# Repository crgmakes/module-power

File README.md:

# Simple Power Module

All the source files for the simple power module hardware. This module converts 120VAC or 240VAC to 5VDC @ 2A and also provides 3.3V @ 3A.

# Software 

You will need [KiCad](https://kicad.org) to view and edit this design. Click [here](https://www.kicad.org/download/) to download.

You will also need all the associated libraries and models to drive the design if you want to make changes or view the 3D rendering:

https://github.com/crgmakes/kicad-library.git

Kicad MUST be configured properly to use all the files in this repo. Once you have Kicad installed, under Preferences->Configure Paths..., make the following entries:

1 - KICAD_USER_DIR -> set to the root location of where you placed the above repository.
2 - KICAD_USER_LIBRARY = ${KICAD_USER_DIR}/Library
3 - KICAD_USER_MODEL_DIR = ${KICAD_USER_LIBRARY}/models
4 - KICAD_USER_TEMPLATE_DIR	= ${KICAD_USER_LIBRARY}/templates	

Kicad will operate mostly normally if these are not set properly. You will notice an issue when you view the PCB in 3D mode.

***NOTE***: after makeing a release build in git, if your rendered 3D images are missing components, ensure the path to EVERY component model is set to ${KICAD_USER_MODEL_DIR}/<model name>.

Kicad sometimes replaces the variable with an expansion and that FAILS during the build process because the expanded variable is local and does not match the build environment.

---

THE DESIGN IS PROVIDED "AS IS" AND THE AUTHOR DISCLAIMS ALL WARRANTIES WITH REGARD TO THIS DESIGN INCLUDING ALL IMPLIED WARRANTIES OF MERCHANTABILITY AND FITNESS. IN NO EVENT SHALL THE AUTHOR BE LIABLE FOR ANY SPECIAL, DIRECT, INDIRECT, OR CONSEQUENTIAL DAMAGES OR ANY DAMAGES WHATSOEVER RESULTING FROM LOSS OF USE, DATA OR PROFITS, WHETHER IN AN ACTION OF CONTRACT, NEGLIGENCE OR OTHER TORTIOUS ACTION, ARISING OUT OF OR IN CONNECTION WITH THE USE OR PERFORMANCE OF THIS DESIGN.

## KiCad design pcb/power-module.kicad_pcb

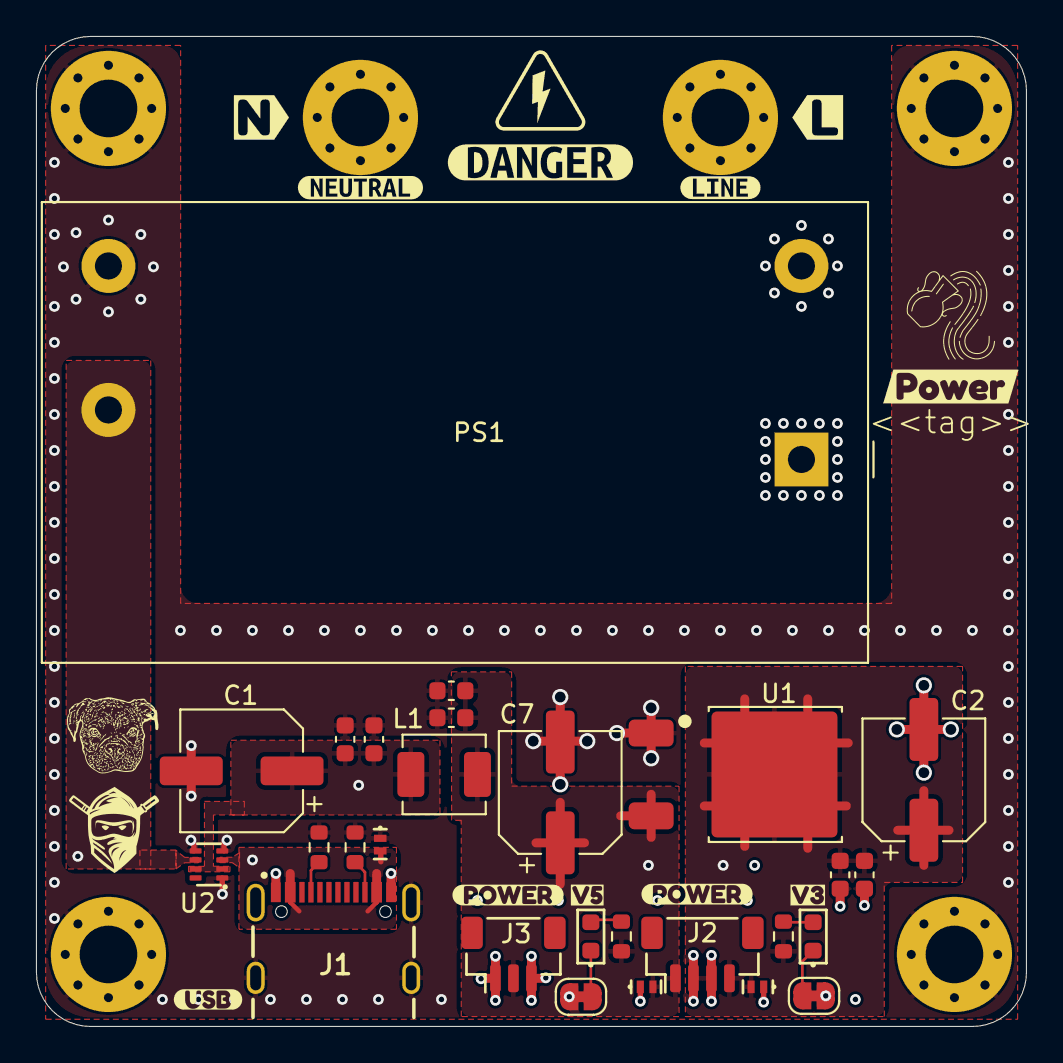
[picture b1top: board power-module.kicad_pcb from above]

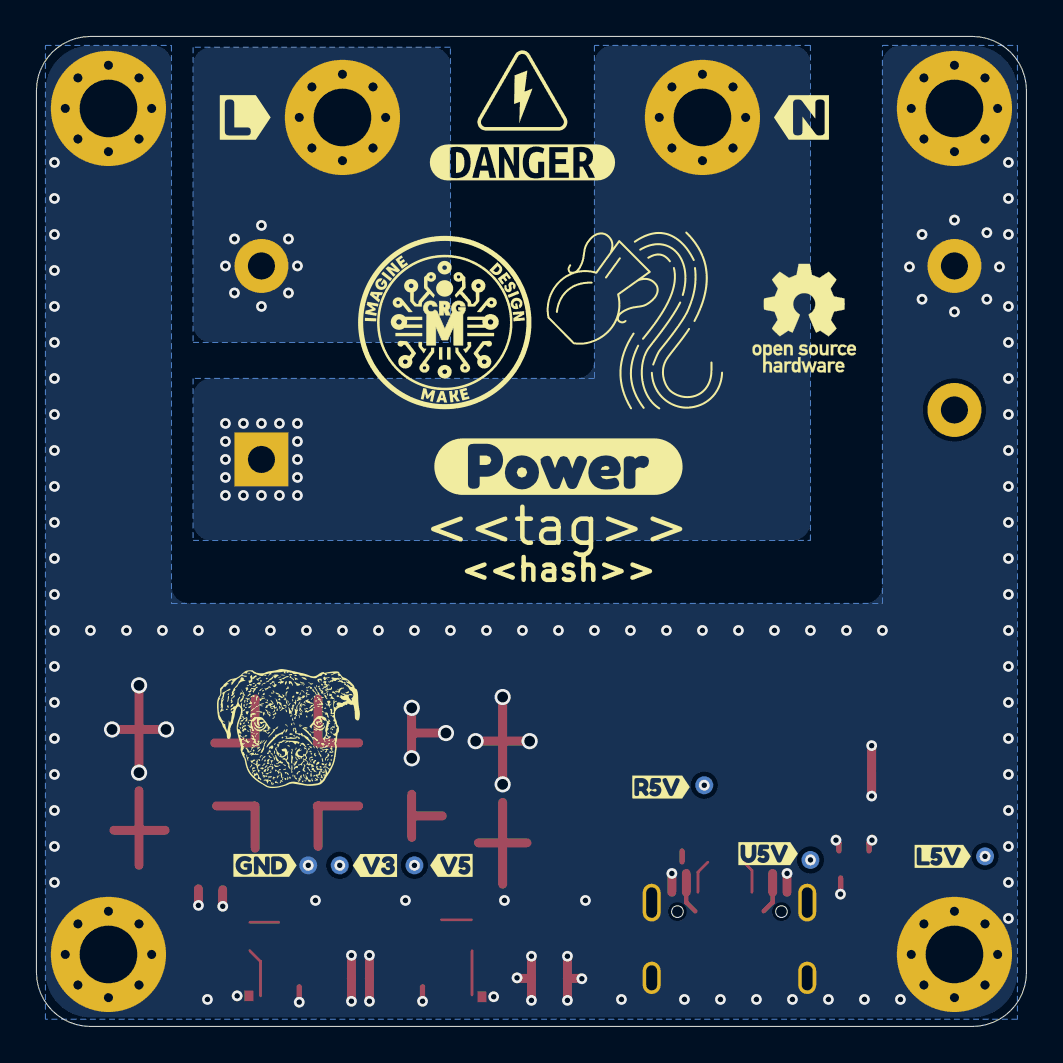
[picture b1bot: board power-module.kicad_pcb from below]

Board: 4 copper layers, 55.0 x 55.0 mm, 69 parts (21 on the bottom side), 14 nets.

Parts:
C1, C2, C7: 220uF; CP_Elec_6.3x5.4
C3, C4, C5, C6, C9, C10: 10uF; C_0603_1608Metric
D1, D4: PESD5V5C1BL; DFN1006-2
D2, D3: Orange; LED_0603_1608Metric
D5: PESD3V3S1BL; DFN1006-2
H1, H2, H3, H4, H5, H6: MountingHole_Pad; MountingHole_3.2mm_M3_Pad_Via
J1: USB_C_PowerOnly_6P; GCT_USB4105-GF-A
J2: JST_SH_BM04B-SRSS-TB_1x04-1MP_P1.00mm_Vertical
J3: BM03B-SRSS-TB; JST_SH_BM03B-SRSS-TB_1x03-1MP_P1.00mm_Vertical
JP1, JP2: SolderJumper-2_P1.3mm_Bridged_RoundedPad1.0x1.5mm
L1: 2.2u; L_Sunlord_MWSA0402S
LOGO1: CRGM Logo 10mm
LOGO2: OSHW-Logo_5.7x6mm_SilkScreen
LOGO3: Aquarius Logo 10mm
LOGO4: Aquarius Logo 5mm
LOGO5: Roxy 8mm
LOGO6: FNWW Face 5mm
LOGO7: Roxy 5mm
PS1: IRM-10-5; Converter_ACDC_MeanWell_IRM-10-xx_THT
R1, R2: 5.1K; R_0603_1608Metric
R3, R4: 4.7k; R_0603_1608Metric
S1, S2: HIGH-VOLTAGE-5MM
TP1: V5; TestPoint_Pad_D1.0mm
TP2: RAW_5V; TestPoint_Pad_D1.0mm
TP3: V33; TestPoint_Pad_D1.0mm
TP4: LINE_5V; TestPoint_Pad_D1.0mm
TP5: USB_5V; TestPoint_Pad_D1.0mm
TP6: GND; TestPoint_Pad_D1.0mm
U1: AZ1084-3.3; TO-252-2
U2: LM66200DRLR; SOTFL50P160X60-8N
kibuzzard-67E1D06C, kibuzzard-67E1D06C#2: G***; kibuzzard-67E1D06C
kibuzzard-67F465A8: G***; kibuzzard-67F465A8
kibuzzard-6927C46E: G***; kibuzzard-6927C46E
kibuzzard-6927C47C: G***; kibuzzard-6927C47C
kibuzzard-6927C51A: G***; kibuzzard-6927C51A
kibuzzard-6927C68A: G***; kibuzzard-6927C68A
kibuzzard-6927C80C: G***; kibuzzard-6927C80C
kibuzzard-6927C83D: G***; kibuzzard-6927C83D
kibuzzard-6927C468: G***; kibuzzard-6927C468
kibuzzard-6927C483: G***; kibuzzard-6927C483
kibuzzard-6927C813: G***; kibuzzard-6927C813
kibuzzard-6952B9DD: G***; kibuzzard-6952B9DD
kibuzzard-6952BA1D: G***; kibuzzard-6952BA1D
kibuzzard-6952BA23: G***; kibuzzard-6952BA23
kibuzzard-692877B5: G***; kibuzzard-692877B5
kibuzzard-692877CC: G***; kibuzzard-692877CC
kibuzzard-692877DB: G***; kibuzzard-692877DB
kibuzzard-692877E6: G***; kibuzzard-692877E6
kibuzzard-692885AF: G***; kibuzzard-692885AF
kibuzzard-68084394: G***; kibuzzard-68084394

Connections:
+3.3V: C2.1, C9.1, C10.1, D5.2 (K2), J2.4, R4.1, TP3.1, U1.2 (VO)
+5V: C5.1, C6.1, C7.1, D4.2 (K2), J2.1, J3.2, L1.2, R3.1, TP1.1, U1.3 (VI)
/Power/AC_L: H1.1, PS1.2 (AC/L)
/Power/AC_N: H2.1, PS1.1 (AC/N)
/Power/CC1: J1.A5 (CC1), R2.1
/Power/CC2: J1.B5 (CC2), R1.1
/Power/V3.3LED: D2.2 (A), R4.2
/Power/V5LED: D3.2 (A), R3.2
GND: C1.2, C2.2, C3.2, C4.2, C5.2, C6.2, C7.2, C9.2, C10.2, D1.1 (K1), D4.1 (K1), D5.1 (K1), H3.1, H4.1, H5.1, H6.1, J1.A1B12 (GND), J1.B1A12 (GND), J1.S1 (SHIELD), J2.2, J2.3, J3.1, J3.3, JP1.1 (A), JP2.1 (A), PS1.3 (-Vo), R1.2, R2.2, TP6.1, U1.1 (GND), U2.1 (GND1), U2.4 (~ON), U2.5 (GND2)
LINE_5V: PS1.4 (+Vo), TP4.1, U2.6 (VIN2)
unnamed: D2.1 (K), JP2.2 (B)
unnamed: D3.1 (K), JP1.2 (B)
RAW_5V: C1.1, C3.1, C4.1, L1.1, TP2.1, U2.2 (VOUT1), U2.7 (VOUT2)
USB_5V: D1.2 (K2), J1.A4B9 (VBUS), J1.B4A9 (VBUS), TP5.1, U2.3 (VIN1)

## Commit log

2025-04-09 Updated foot prints; maybe deprecated
2025-04-09 Initial checkin
2025-04-10 Attribute updates; generated production files
2025-04-11 Updated silkscreen and LED size
2025-04-29 Changed switching mechanism; updated power delivery for v3.3
2025-05-08 Fixed AZ1084 footprint
    Fixed USB-C Connector / symbol mismatch
    Moved parts around
    Moved USB-C connector from overhanging.
    Generated ibom.
2025-05-08 Renamed to power-module; updated silkscreen and some symbols
2025-05-10 generated fabrication files
2025-05-14 Changed LED colors; regenerated panels
2025-05-15 Added additional file types
2025-05-15 Changed to vscore instead of mouse bites
    re-panelized.
2025-05-16 First check in of CI/CD files
2025-05-16 Updated connector symbol and back annotation
2025-05-16 added director to workflow script
2025-05-16 fixed name of workflow file
2025-05-16 backed out directory; added verbose
2025-05-16 fixed yaml file name AGAIN!
2025-05-16 added path back in to various locations in ERC
2025-05-16 updated all paths
2025-05-16 Failed to update all directory paths
2025-05-16 revamped using different examples
2025-05-16 fixed path typo
2025-05-16 further debugging required
2025-05-16 force execution of swapping commit variable
2025-05-16 getting tired doing it this way....
2025-05-16 optimized script; still fighting some errors
2025-05-16 removed ignore_unconnected
2025-05-17 Reordered tasks most important to least; added sub directories
2025-05-17 Updated parameters on some parts
2025-05-17 cleaning up ibom settings
2025-05-17 fixed typo
2025-05-17 added fontconfig and checkoutv4
2025-05-17 Added extras and crgm lib.
2025-05-17 fixed typo in checkout parameters
2025-05-17 attempting to set user library via environment variable
2025-05-17 trying again with different syntax
2025-05-17 trying again
2025-05-17 i think i have it
2025-05-17 well, maybe not.
2025-05-17 add models directory
2025-05-17 still trying to resolve library issues - env does not seem to be working
2025-05-17 Changed zoom level; added fonts to extras
2025-05-17 continue to resolve library issues (pcbdraw)
2025-05-17 fixed syntax error with pcbdraw lib
2025-05-17 adjusting directories
2025-05-17 chugging away at directory and library hell
2025-05-17 reverted director change
2025-05-18 removed zoom level less than 1
2025-05-18 Clean up - removed unnecessary steps
2025-05-18 Updated to use full images with blender
2025-05-18 tweaked blender settings
2025-05-18 moved output to proper location
2025-05-18 fixed type causing errors; amplified blender options
2025-05-18 Updated models and alignment
2025-05-18 Broke something - not sure what; roll back changes.
2025-05-18 fixed another typo
2025-05-18 Directory name changes to get models working
2025-05-18 fixed formatting error for rotations
2025-05-18 fixed model expansion of usb connector; changed script to use sed
2025-05-18 fixed path error in sed
2025-05-18 turned off downloading of models as sanity check
2025-05-18 Adjusting path for models dir
2025-05-18 still adjusting
2025-05-20 Adjusting settings to replicate manual input
2025-05-20 continue tweaking settings
2025-05-20 continuing to debug -- getting closer
    have custom models now; can't find stock models.
2025-05-22 pulled 3d libraries
2025-05-22 changed gitlab repo for models
2025-05-22 moved to explicit unix command from workflow runner
2025-05-22 fixed directory name erro
2025-05-22 oh my g*d I can't type
2025-05-24 Added panelization; cleaned up
2025-05-24 changed zipping at output of fab
2025-05-24 Updated zip path
2025-05-24 Broke zip out into separate step
2025-05-24 changed zip format again
2025-05-24 remove some steps to save time
2025-05-24 removed lfs
2025-05-24 removed listing some directories
2025-05-24 switched to zip action
2025-05-24 fixed formatting error
2025-05-24 changed syntax; removed step to save time
2025-05-24 set working directory
2025-05-24 finally found the actual problem
2025-05-24 fixed path problem with artifact upload
2025-05-24 changed paths; uncommented everything
2025-05-24 switched to fab kit to capture rotations
2025-05-24 added path to fabkit
2025-05-24 added debug statement
2025-05-24 added debug
2025-05-24 further debugging
2025-05-24 still debugging
2025-05-24 fixed path issues
2025-05-24 debugging filename path
2025-05-24 adjusted file name path
2025-05-24 full workflow testing
2025-05-24 pwd doesn't work?
2025-05-25 clean up; fixing directories
2025-05-25 fixed kibot yaml
2025-05-25 Fixed variants
2025-05-25 fixed dup mkdir
2025-05-25 updated directories
2025-05-25 changed file names
2025-05-25 Overhauled scripts - changed to checkin vs release
2025-05-25 moved ibom to directory; zipped gerbers
2025-05-25 fixed run paths
2025-05-25 fixed back option for zip of gerbers
2025-05-25 Updated retention days for artifacts
2025-05-25 adjusted gerber directories
2025-05-25 switched to fabkit for single pcb
2025-05-25 only copy pcb and sch to pcb directory
2025-05-25 checking testing file
2025-05-25 more testing
2025-05-25 add additional checkout
2025-05-25 added dir to check out
2025-05-25 testing two jobs
2025-05-25 testing multiple jobs
2025-05-25 testing calling selected targets
2025-05-25 fixed path to include file
2025-05-26 fixed model locations in pcb; reworking to use import
2025-05-26 fixed model name and locations
2025-05-26 Using imports - first real test
2025-05-26 updated directories for git
2025-05-26 fixed directory
2025-05-26 fixed upload artifacts directory
2025-05-26 more directory fixing bs
2025-05-26 debugging artifact directory problem
2025-05-26 more debugging
2025-05-26 fixed directory error
2025-05-26 still fighting directory issues
2025-05-26 testing ibom
2025-05-26 Fixed ibom by adding preflight
2025-05-26 added panel options
2025-05-26 Added panelize
2025-05-26 fixed panel file name
2025-05-26 Fixed soldermask on USB connector; cleaned up scripts
2025-05-26 Fixed name issue with artifact upload
2025-05-26 Fixed USB model path and position, and TO-252 position
2025-05-26 Added release to run type
2025-05-26 Testing with using env variable for home directory
2025-05-26 testing release without releasing
2025-05-26 Updated test file for rendering
2025-05-26 Updated directories and release process
2025-05-27 changed release file naming to include tag
2025-05-27 alternate inductor - primary is out of stock
2025-05-28 Changed build to only happen manually or during a release
    Only builds simple fab files on demand now
    Commented script more for clarity
    Swapped out {{github.workspace}} for GITHUB_WORKSPACE
2025-05-28 Part swap; moved from 2x2 panel to 1x2 panel
2025-05-29 Added tag to pcb to capture version on release; updated check in script to fill in tag
2025-05-31 Separated 22uF into two 10uF; rerouted everything for better layout
2025-05-31 flattened artifact and release directories
2025-05-31 Fixed file name in script; fixed H3 name missing in schematic
2025-05-31 fixed directory for released panel
2025-05-31 still resolving directory issues with panel release
2025-05-31 Changed name of module to reflect release trigger
2025-05-31 temporarily disabled release if
2025-05-31 re-enabled if
2025-05-31 Removed debugging from release script; renamed script file
2025-06-01 Added dimensions to PCB
2025-06-21 Updated resistor values
2025-06-21 Minor clean up and dimensioning
2025-06-21 Updated mounting hole footprint and dimensions
2025-06-21 Updated layers
2025-06-22 Added second power connector and TP for GND
2025-06-22 Changed to multi-sheet
2025-06-26 Updated frame template
2025-06-27 Updated worksheet template
2025-06-27 Updated worksheet template and logo
2025-06-27 Updated CI script
2025-07-13 Update license and PCB schematic details
    Clarified KiCAD library licensing in LICENSE.md to reference the kicad-library repo. Added a PCB specification text box to requirements.kicad_sch. Updated image data in power-module.kicad_sch for imp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
2025-07-24 Updated license
2025-10-26 Updated .gitignore
2025-11-22 Updated netclass error
2025-12-16 Added second power connector
    Rearranged.
    Added additional filtering
2025-12-27 Updated 100uF to 220uF
    Adjusted part numbers
2025-12-29 Changed power connnectors
    Changed to 3 pin power connector for +5v only.
    Power input limited to AC or USB only
    Added 220uF cap to 3.3v out at LDO
    Added TVS to power connectors
2025-12-29 Fixed connector spacing
2026-03-01 replaced .wrl with .step
